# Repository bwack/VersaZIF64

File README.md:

# VersaZIF64

For gerbers please click the releases tab.
This project is based on the [Versa64Cart project](https://github.com/bwack/Versa64Cart).

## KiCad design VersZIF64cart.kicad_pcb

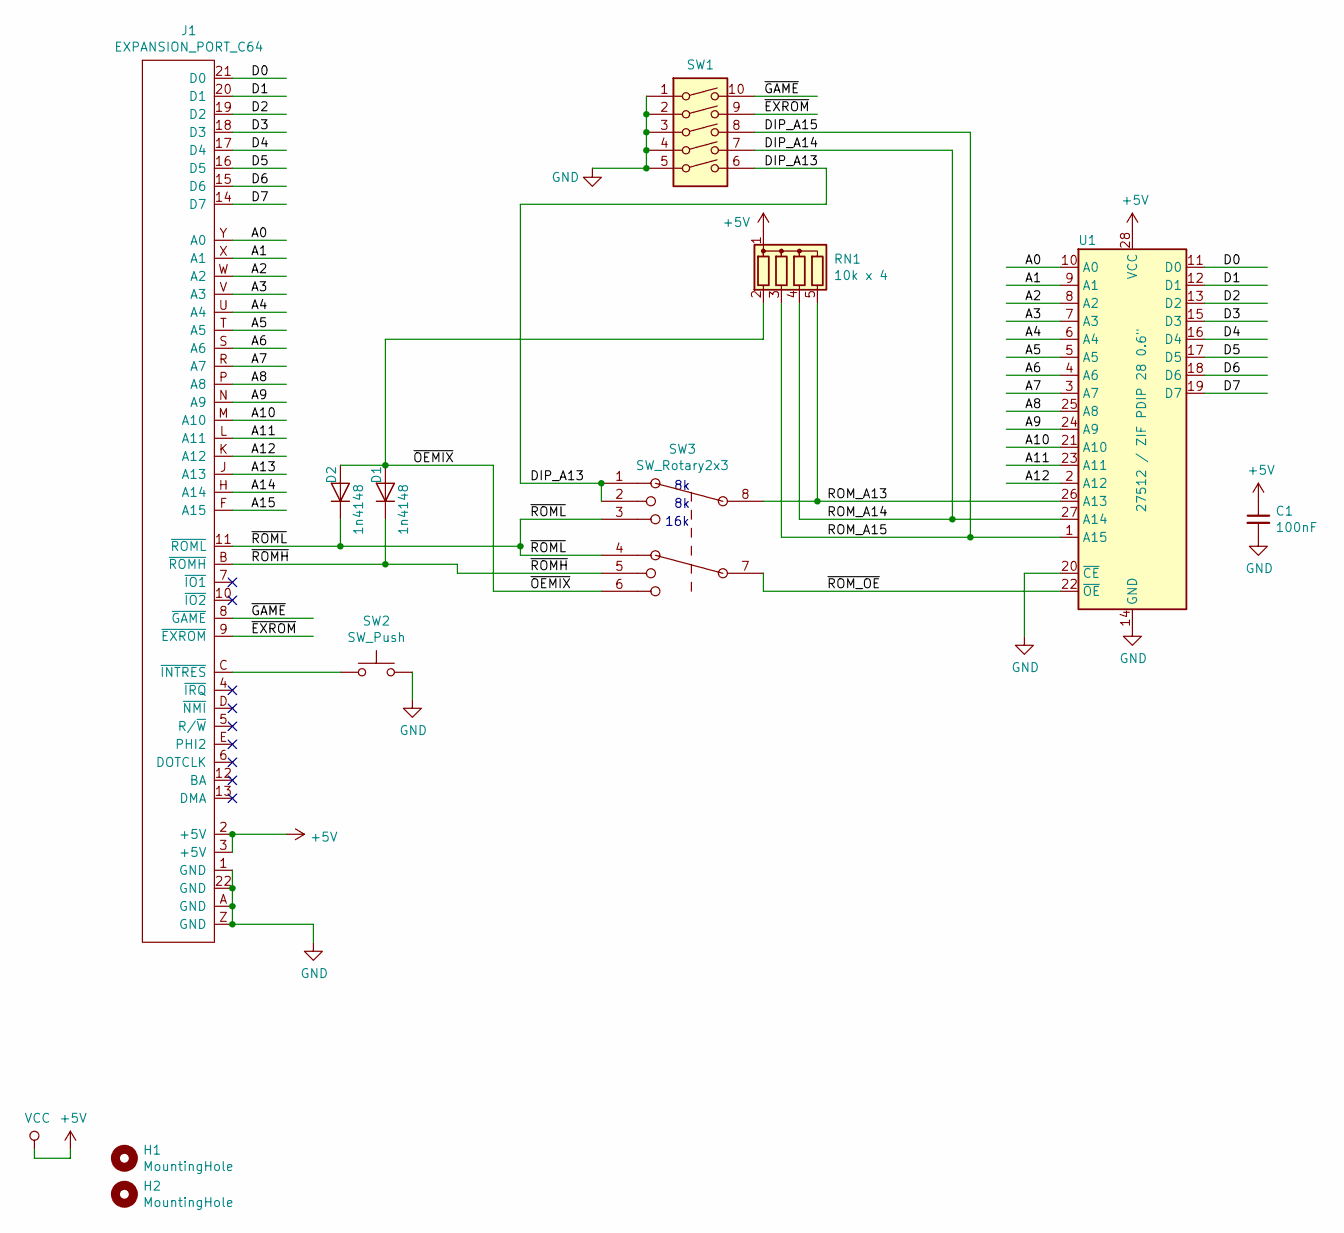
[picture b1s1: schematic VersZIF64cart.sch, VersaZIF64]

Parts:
C1: 100nF; C_Disc_D3.8mm_W2.6mm_P2.50mm
D1, D2: 1n4148; D_DO-35_SOD27_P7.62mm_Horizontal
H1, H2: MountingHole; MountingHole_4.3mm_M4_ISO7380
J1: EXPANSION_PORT_C64; C64_EXPANSION_PORT
RN1: 10k x 4; R_Array_SIP5
SW1: SW_DIP_x05; SW_DIP_SPSTx05_Slide_9.78x14.88mm_W7.62mm_P2.54mm
SW2: SW_Push; SW_PUSH_6mm_H5mm
SW3: SW_Rotary2x3; Nidec_SS-10-23NP-L-E_RotarySwitch_2x3
U1: 27512 / ZIF PDIP 28 0.6\"; DIP_Socket-28_W11.9_W12.7_W15.24_W17.78_W18.5_3M_228-1277-0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

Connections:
+5V: C1.1, J1.2 (+5V), J1.3 (+5V), RN1.1 (common), U1.28 (VCC)
/A0: J1.Y (A0), U1.10 (A0)
/A1: J1.X (A1), U1.9 (A1)
/A2: J1.W (A2), U1.8 (A2)
/A3: J1.V (A3), U1.7 (A3)
/A4: J1.U (A4), U1.6 (A4)
/A5: J1.T (A5), U1.5 (A5)
/A6: J1.S (A6), U1.4 (A6)
/A7: J1.R (A7), U1.3 (A7)
/A8: J1.P (A8), U1.25 (A8)
/A9: J1.N (A9), U1.24 (A9)
/A10: J1.M (A10), U1.21 (A10)
/A11: J1.L (A11), U1.23 (A11)
/A12: J1.K (A12), U1.2 (A12)
/A13: J1.J (A13)
/A14: J1.H (A14)
/A15: J1.F (A15)
/D0: J1.21 (D0), U1.11 (D0)
/D1: J1.20 (D1), U1.12 (D1)
/D2: J1.19 (D2), U1.13 (D2)
/D3: J1.18 (D3), U1.15 (D3)
/D4: J1.17 (D4), U1.16 (D4)
/D5: J1.16 (D5), U1.17 (D5)
/D6: J1.15 (D6), U1.18 (D6)
/D7: J1.14 (D7), U1.19 (D7)
/DIP_A13: SW1.6, SW3.1, SW3.2
/DIP_A14: RN1.4 (R3), SW1.7, U1.27 (A14)
/DIP_A15: RN1.3 (R2), SW1.8, U1.1 (A15)
/ROM_A13: RN1.5 (R4), SW3.8, U1.26 (A13)
/~EXROM~: J1.9 (~EXROM~), SW1.9
/~GAME~: J1.8 (~GAME~), SW1.10
/~OEMIX~: D1.2 (A), D2.2 (A), RN1.2 (R1), SW3.6
/~ROMH~: D1.1 (K), J1.B (~ROMH~), SW3.5
/~ROML~: D2.1 (K), J1.11 (~ROML~), SW3.3, SW3.4
/~ROM_OE~: SW3.7, U1.22 (~OE)
GND: C1.2, J1.1 (GND), J1.22 (GND), J1.A (GND), J1.Z (GND), SW1.1, SW1.2, SW1.3, SW1.4, SW1.5, SW2.2, U1.14 (GND), U1.20 (~CE)
unnamed: J1.C (~INTRES~), SW2.1

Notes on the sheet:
16k

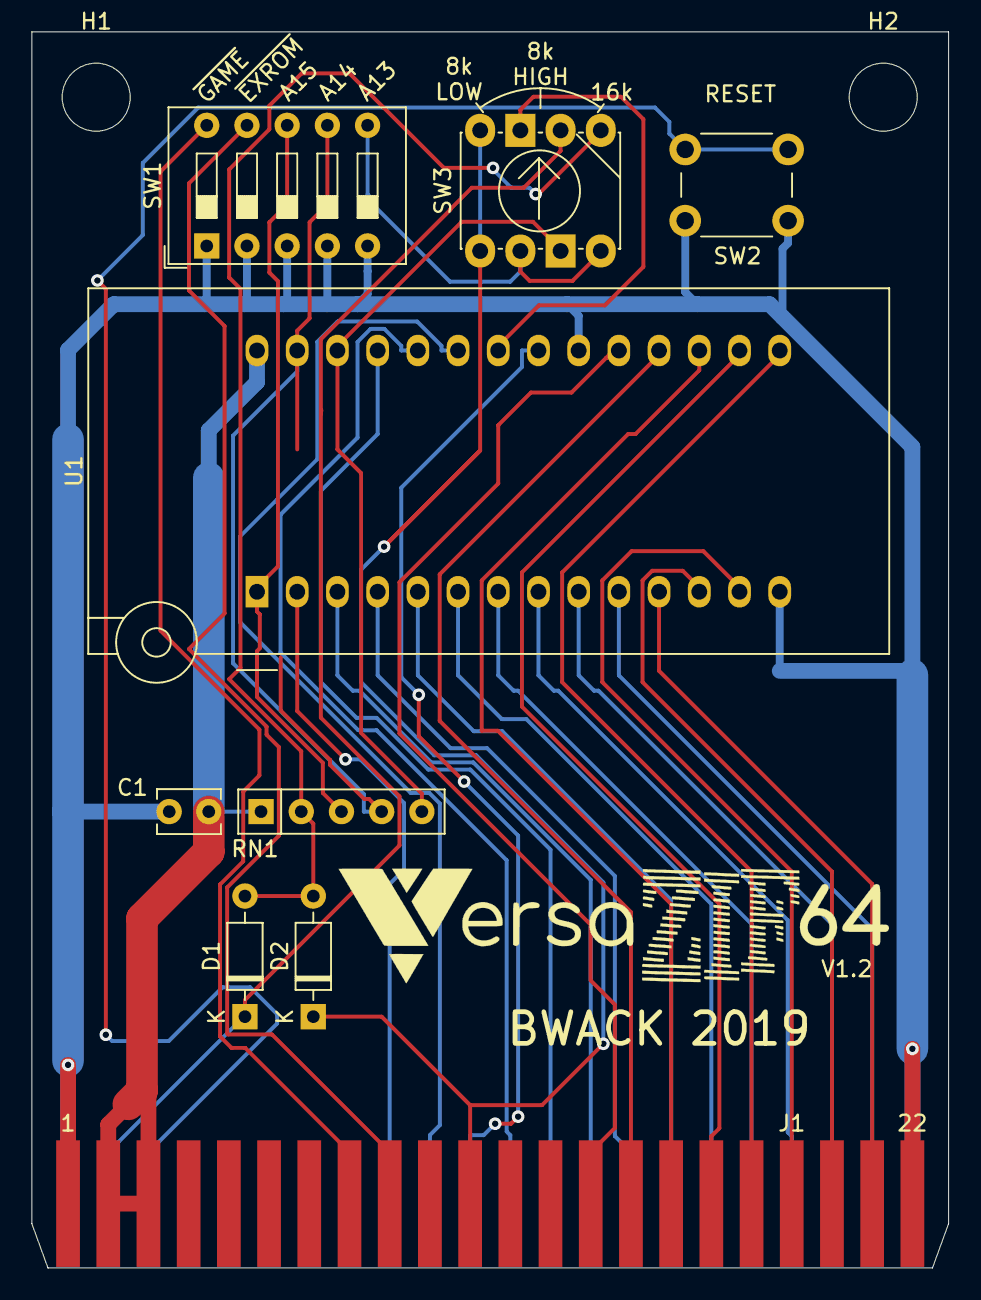
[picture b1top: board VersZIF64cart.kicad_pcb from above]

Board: 2 copper layers, 57.9 x 78.1 mm, 11 parts (0 on the bottom side), 34 nets.

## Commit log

2019-06-22 pdf and 3D drawing
2019-06-28 V1.1
2019-07-08 VersaZIF64 1.2
2019-07-08 Gerbers
2019-07-08 1.2 3d image.
2019-07-08 rename
